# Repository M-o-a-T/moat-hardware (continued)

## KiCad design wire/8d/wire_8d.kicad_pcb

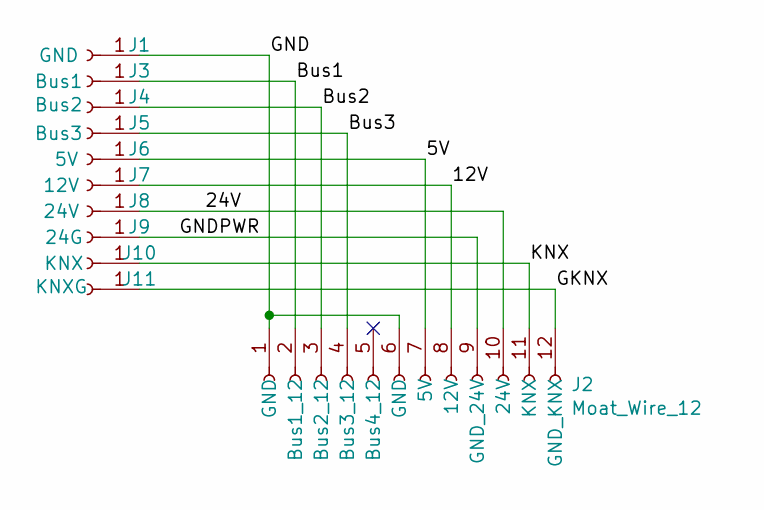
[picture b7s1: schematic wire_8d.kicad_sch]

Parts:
J1: GND; SolderWirePad_1x01_SMD_1x2mm
J2: Moat_Wire_12; MoaT_12_Pin_H
J3: Bus1; SolderWirePad_1x01_SMD_1x2mm
J4: Bus2; SolderWirePad_1x01_SMD_1x2mm
J5: Bus3; SolderWirePad_1x01_SMD_1x2mm
J6: 5V; SolderWirePad_1x01_SMD_1x2mm
J7: 12V; SolderWirePad_1x01_SMD_1x2mm
J8: 24V; SolderWirePad_1x01_SMD_1x2mm
J9: 24G; SolderWirePad_1x01_SMD_1x2mm
J10: KNX; SolderWirePad_1x01_SMD_1x2mm
J11: KNXG; SolderWirePad_1x01_SMD_1x2mm

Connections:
/5V: J2.7 (5V), J6.1
/12V: J2.8 (12V), J7.1
/24V: J2.10 (24V), J8.1
/Bus1: J2.2 (Bus1_12), J3.1
/Bus2: J2.3 (Bus2_12), J4.1
/Bus3: J2.4 (Bus3_12), J5.1
/GKNX: J2.12 (GND_KNX), J11.1
/GND: J1.1, J2.1 (GND), J2.6 (GND)
/GNDPWR: J2.9 (GND_24V), J9.1
/KNX: J2.11 (KNX), J10.1

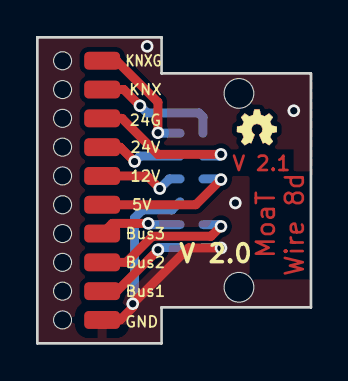
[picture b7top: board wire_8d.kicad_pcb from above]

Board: 2 copper layers, 15.2 x 17.0 mm, 11 parts (1 on the bottom side), 10 nets.

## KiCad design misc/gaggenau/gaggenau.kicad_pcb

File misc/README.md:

This directory contains random schematics etc.

== usb-int

A board to interrupt power and data to a USB device.

Two versions; one has external GPIO inputs, the other contains a hub and a
USB-to-GPIO controller.

== enocean-switch

A simple remote-controlled power switch, with an ESP12 controller and a TCM310
enocean radio. Wired as a simple L-N-L' three-wire terminal.

== esp-switch

A simple remote-controlled power switch, with an ESP12 controller. Wired for
two L-PE-N screw terminals, one in and one out. Used for heating control,
with I²C-connected thermometers.

== opto-switch

A simple board to interrupt a control line.

Available in "plus" and "minus" variants, interrupting the positive vs.
negative wire.

== espmini

A simple breakout board for an ESP-12S module that can be installed in
WLAN-connected plugs.

== enocean-rs485

A gateway between Enocean and RS485, for controlling SEW Eurodrive inverters.

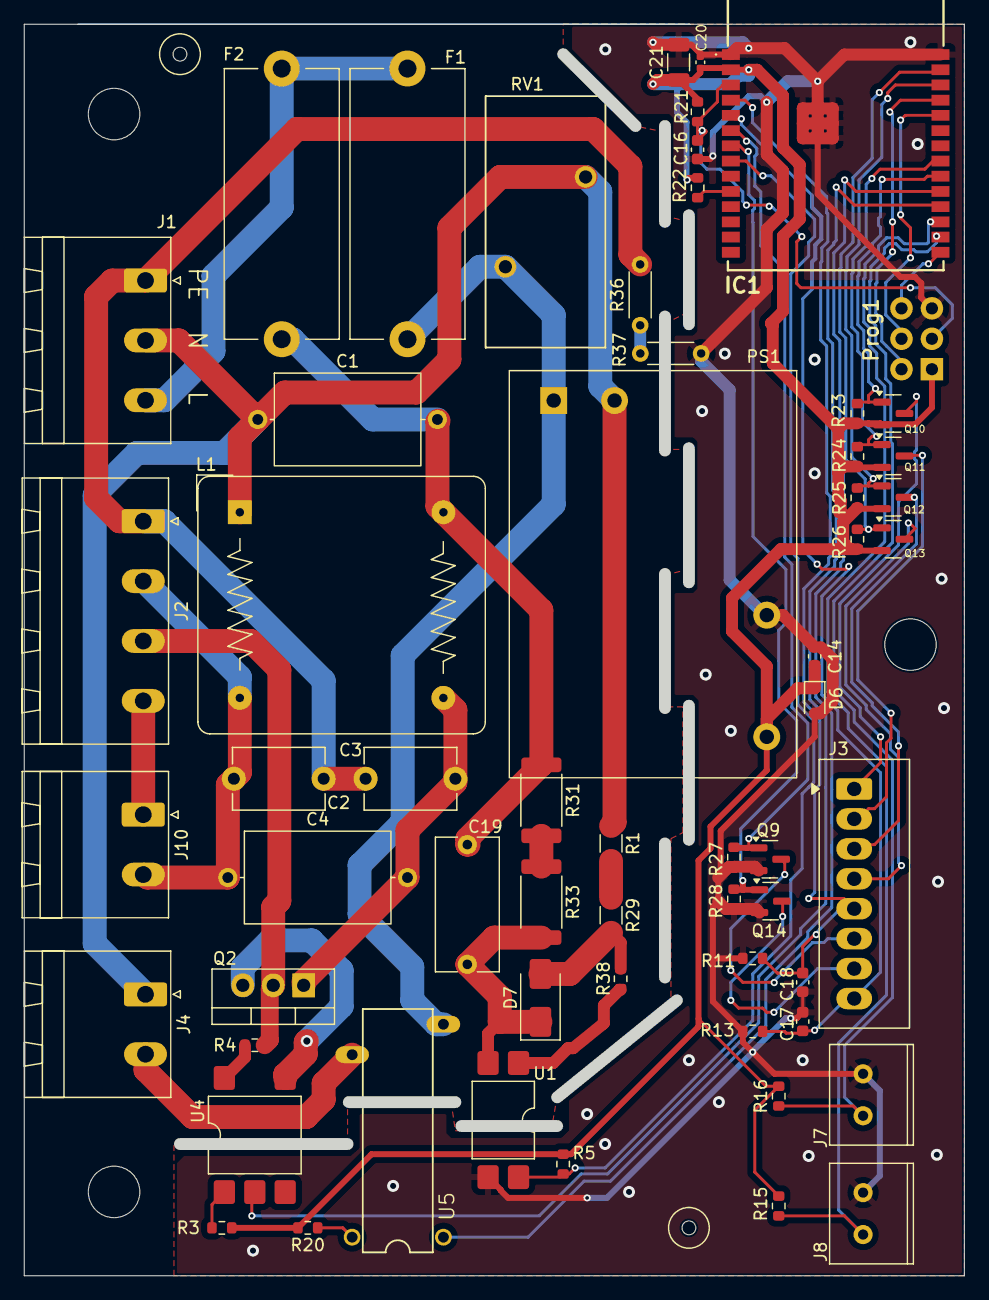
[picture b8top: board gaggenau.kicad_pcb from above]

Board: 2 copper layers, 77.6 x 103.6 mm, 60 parts (0 on the bottom side), 46 nets.

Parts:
C1, C4: 470nF; C_Axial_L12.0mm_D7.5mm_P15.00mm_Horizontal
C2, C3: 4.7nF; C_Disc_D7.5mm_W5.0mm_P7.50mm
C14: 10µF; C_0603_1608Metric
C16: 10nF; C_0603_1608Metric
C17, C18: 1nF; C_0603_1608Metric
C19: 220nF 400V X2; C_Rect_L11.0mm_W5.1mm_P10.00mm_MKT
C20: 100nF; C_0402_1005Metric
C21: 22µF; C_1206_3216Metric
D6: P6KE6.8A; D_SOD-323
D7: SMAJ5.0CA; D_SMA
F1, F2: FuseHolder; Fuseholder_Cylinder-5x20mm_Stelvio-Kontek_PTF78_Horizontal_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
IC1: ESP32-C6-WROOM-1-N8; ESP32C6WROOM1N8
J1: Mains; PhoenixContact_MSTBA_2,5_3-G_1x03_P5.00mm_Horizontal
J2: Vent; PhoenixContact_MSTBA_2,5_4-G_1x04_P5.00mm_Horizontal
J3: Conn_01x08_Socket; TerminalBlock_8
J4: Light; PhoenixContact_MSTBA_2,5_2-G_1x02_P5.00mm_Horizontal
J7: ?; Würth3.5mm_2
J8: ? Klemmen; Würth3.5mm_2
J10: Cap; PhoenixContact_MSTBA_2,5_2-G_1x02_P5.00mm_Horizontal
L1: 6mH; Choke
PS1: Apos03; Hiecube AP05-Zero
Prog1: PogoPad; 2X3-NS
Q2: BTB16-600BW; TO-220-3_Vertical
Q9, Q14: Q_NMOS; SOT-23
Q10, Q11, Q12, Q13: 2301V; SOT-23
R1, R29: 47; R_1206_3216Metric
R3, R38: 220; R_0603_1608Metric
R4, R15, R16: 1k; R_0603_1608Metric
R5: 47k; R_0603_1608Metric
R11, R13: 470; R_0603_1608Metric
R20: 360; R_0603_1608Metric
R21, R22: 10k; R_0603_1608Metric
R23, R24, R25, R26, R27, R28: 100k; R_0603_1608Metric
R31: 470k 200V; R_2512_6332Metric
R33: 470k 100V; R_2512_6332Metric
R36, R37: 1M; R_Axial_DIN0204_L3.6mm_D1.6mm_P5.08mm_Horizontal
RV1: Varistor230V; Varistor_Disc_D21mm_W10mm_P7.5mm
U1: PC814; SMDIP-4_W9.53mm
U4: KMOC302S; SMDIP-6_W9.53mm
U5: CPC1965G; DIL16-CPC1965G

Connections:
/Boot: IC1.15 (IO9), Prog1.6 (Boot0)
/Btn1: IC1.20 (IO22), Q10.1 (G), R23.1
/Btn2: IC1.21 (IO23), Q11.1 (G), R24.1
/Btn3: IC1.26 (IO3), Q12.1 (G), R25.1
/Btn4: IC1.27 (IO2), Q13.1 (G), R26.1
/Btn5: C17.1, IC1.4 (IO4), J3.5, R11.2
/Btn6: C18.1, IC1.5 (IO5), J3.8, R13.2
/Btn7: IC1.6 (IO6), Q9.1 (G), R27.1
/Btn8: IC1.7 (IO7), Q14.1 (G), R28.1
/EN: C16.1, IC1.3 (EN), Prog1.3 (Reset), R21.1
/Ivent: IC1.8 (IO0), R5.2, U1.4
/Kblau: J3.1, Q10.3 (D)
/Kbraun: J3.7, Q14.3 (D)
/Kgrau: J3.3, Q12.3 (D)
/Kgrün: J3.4, Q13.3 (D)
/Krot: J3.6, Q9.3 (D)
/Kweiß: J3.2, Q11.3 (D)
/L: F1.2, F2.2, J1.3
/Lf: F1.1, PS1.1 (L), RV1.1, U5.8 (A2)
/Lf2: C1.2, C19.1, F2.1, L1.3, R31.1
/Llight: J4.2, U5.10 (A1)
/Lvent: J2.3, Q2.2 (A2), R4.1
/Lx: C3.2, C4.2, L1.4, Q2.1 (A1)
/N: C1.1, J1.2, J4.1, L1.1, PS1.2 (N), R1.1, RV1.2
/Nx: C2.1, C4.1, J2.2, J10.2, L1.2
/OVent: IC1.18 (IO20), U4.2
/Olight: IC1.19 (IO21), U5.1 (-)
/PB1: IC1.16 (IO18), J7.1, R16.2
/PB2: IC1.17 (IO19), J8.1, R15.2
/Rx: IC1.24 (RXD0), Prog1.4 (Rx)
/Tx: IC1.25 (TXD0), Prog1.2 (Tx)
Earth_Protective: C2.2, C3.1, J1.1, J2.1, R36.2
GND: C14.2, C16.2, C17.2, C18.2, C20.2, C21.2, D6.2 (A2), IC1.1 (GND_1), IC1.28 (GND_2), IC1.29 (GND_3), IC1.30 (GND_4), IC1.31 (GND_5), IC1.32 (GND_6), IC1.33 (GND_7), IC1.34 (GND_8), IC1.35 (GND_9), IC1.36 (GND_10), IC1.37 (GND_11), J7.2, J8.2, PS1.4 (DC-), Prog1.5 (GND), Q9.2 (S), Q14.2 (S), R11.1, R13.1, R27.2, R28.2, R37.1, U1.3
unnamed: C19.2, D7.1 (A1), R33.2, U1.2
unnamed: D7.2 (A2), R29.2, R38.2
unnamed: IC1.10 (IO8), R22.2
unnamed: J2.4, J10.1
unnamed: Q2.3 (G), U4.4
unnamed: R1.2, R29.1
unnamed: R3.1, U4.1
unnamed: R4.2, U4.6
unnamed: R31.2, R33.1
unnamed: R36.1, R37.2
unnamed: R38.1, U1.1
unnamed: R20.1, U5.16 (+)
VCC: C14.1, C20.1, C21.1, D6.1 (A1), IC1.2 (3V3), PS1.3 (DC+), Prog1.1 (+3V), Q10.2 (S), Q11.2 (S), Q12.2 (S), Q13.2 (S), R3.2, R5.1, R15.1, R16.1, R20.2, R21.2, R22.1, R23.2, R24.2, R25.2, R26.2

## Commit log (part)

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2017-08-02 initial check-in
2017-08-02 stupid CRLFs
2017-08-03 Footprints for AVX 9276 push-in connectors
2017-08-03 PCB for servo control
    includes three I/O pins (w/ ADC)
2017-08-03 ignore kicad files
2017-08-03 README
2017-08-07 device and footprint update
2017-08-07 servo update
    ?
2017-08-07 update 2
2017-08-07 New: test board
    test components for 24>3.3V buck converter, I²C boosters
2017-08-07 /test is now a real project directory
    /out is not
2017-08-07 Are *-rescue.lib files valid?
    IMHO not
2017-08-08 servo PCB repaired
2018-09-27 Imported all old files I could find
    This is now kicad 5.0 only.
    All Eagle files have been imported if possible.
2019-05-19 ignore cache
2019-05-19 add a bunch of 3d files
2019-05-19 update local library
2019-05-19 Smoke detector update
2019-05-19 initial check-in of development draft for 16-wire bus plug
2019-05-19 Add fork: heating base plane
2019-09-13 ignore autosave files
2019-09-13 ignore backup files
2019-09-13 Ignore Gerber files
2019-09-13 A heap of mods, not checked in due to laziness
2019-10-29 Breadboard adapter and TE177501x clean up
2019-10-29 Add 3D pogo pin header to contact
2019-10-29 Drop LOCAL3D, replace with :moat3d:
2019-10-29 Fixup espbee
    move driver ICs away from the antenna
2019-10-29 Fix footprint
    TODO fix order numbers
2019-10-29 Heating: fix connector, add OSHW, etc.
2019-10-30 Connectors now say Bus1_12 … Bus14_12
2019-10-30 Hierarchicalize proc
2019-10-30 mistaken checkin
2019-10-30 Add ESP 3D models
2019-10-30 fix espbee 3d footprint
2019-10-30 esp module update
2019-10-30 move smoke_gira
2019-10-30 Library fixup
2019-10-30 Re-worked the Gira thing
2019-10-30 Reorganized the whole library
    Lots to do …
2019-12-18 Too many reworks to count.
    Most notably: Split GND and GNDPWR.
2021-03-02 pi power
2021-12-06 Document bus wire pinouts
2021-12-06 temp check-in before reorg
2021-12-06 Move stuff to old/
2021-12-06 hand solder fixups
2021-12-06 create wire16
2021-12-06 wixup wire_16
2021-12-06 File Rename
2021-12-06 copy wire16 to wire8
2021-12-06 Wire 8 build
2021-12-06 A heap of symbol library fix-ups
2021-12-07 more sym fixes
2021-12-07 Standard baseboard
2021-12-07 Ignore gerber subdir
2021-12-07 wire16 update
2021-12-08 proc_stm32
2021-12-08 Fix 24-pin sockets
    no dot outside the frame
2021-12-10 add small OSHW logos
2021-12-11 A heap of library updates
2021-12-11 deleted nonsense
2021-12-11 format update
2021-12-11 ignore BOMs
2021-12-11 Plug updates
    drop in/out from plug24
2021-12-11 Add programming thingies
2021-12-11 uploads
2022-01-20 PiPower: kicad 6.99 update
2022-01-20 moved
2022-03-05 No save for too long …
2022-03-05 de-JLC
2022-03-05 rename to base_heating
2022-03-05 Fix symbols
2022-03-08 *sigh*
2022-03-08 more misc changes
2022-03-08 file reorg
2022-03-08 Update bus cable assignments
2022-03-08 Re-link
2022-03-08 Rename i2ctemp
2022-03-08 Libraray update for i2ctemp
2022-03-08 empty
2022-03-09 deleted old template
2022-03-09 Updated 2
2022-03-09 Finish rename
2022-05-04 cleanup
2022-05-04 more nice footprints
2022-05-04 more symbols
2022-05-04 wire 8 (10 really), direct
2022-05-04 initial BMS
2022-05-04 simple battery keeper
2022-05-04 simple script to calculate ADC values for a thermistor
2022-05-04 ignore Gerber in addition to gerber
2022-05-04 ignore #auto_saved_files#
2022-05-04 ignore job files
2022-05-24 Library stuff
2022-05-28 BMS stuff update
2022-05-28 temp checkin for readme
2022-05-28 misc updates I didn't bother checking in, oops
2022-05-28 minor fixup
2022-05-28 Added two more config jumpers
2022-09-27 BMS hardware (prev)
2023-07-03 Library update
2023-07-03 base18: config
2023-07-03 ignore JLC production/ folder
2023-07-22 some update
2023-07-27 USB intercept
2023-07-27 BOM stuff
2023-07-27 Add stuff in the "misc" category
2023-07-27 Ignore intermediate XML files
2024-01-06 New board to assume control of a SolvisMax
2024-01-06 Lib update
2024-04-26 some misc/ stuff
2025-08-18 Gaggenau kitchen vent control board
2025-10-07 Save: Gaggenau v1
2025-10-07 One annoying library update later …
2025-10-09 Fix for power supply Hiecube
2025-10-09 Gaggenau replacement v2
2025-10-09 Old check-in: opto-switch-minus
2025-10-09 Project files updated by opening. Bah.
2025-10-09 Old check-in: solvis-control
2025-10-09 Old check-in: ctrl
2025-10-09 Old check-in: base18
2025-10-09 Old check-in: usb-int
2025-10-09 Old check-in: i2ctemp
2025-10-09 Old check-in: enocean-switch
2025-10-09 Old check-in: opto-switch-plus
2025-10-09 Cover thing for battery bars
2025-10-09 Old check-in: esp-switch
2025-10-09 Cover those battery nuts
2025-10-17 BME i2c adapter
2025-10-17 Gaggenau controller update
2025-10-17 Simple 230V AC detector
2025-10-17 Add a couple of breakout adapters
2025-10-17 Add simple three-pole CMOS switch
2025-10-17 Simple 230V SSR switch
2025-10-17 Adapter for minimal ESP8266
    used for replacement controllers in "smart" power strips
2025-10-17 churn
2025-10-17 Controller for a filament spool heater
2025-10-17 Update thermo
2025-10-17 Small Gaggenau update
